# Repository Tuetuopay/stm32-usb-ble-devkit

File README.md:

# STM32 + nRF51 USB & BLE devkit

Small devkit to work with both USB and BLE. Useful for USB Bluetooth gadgets.

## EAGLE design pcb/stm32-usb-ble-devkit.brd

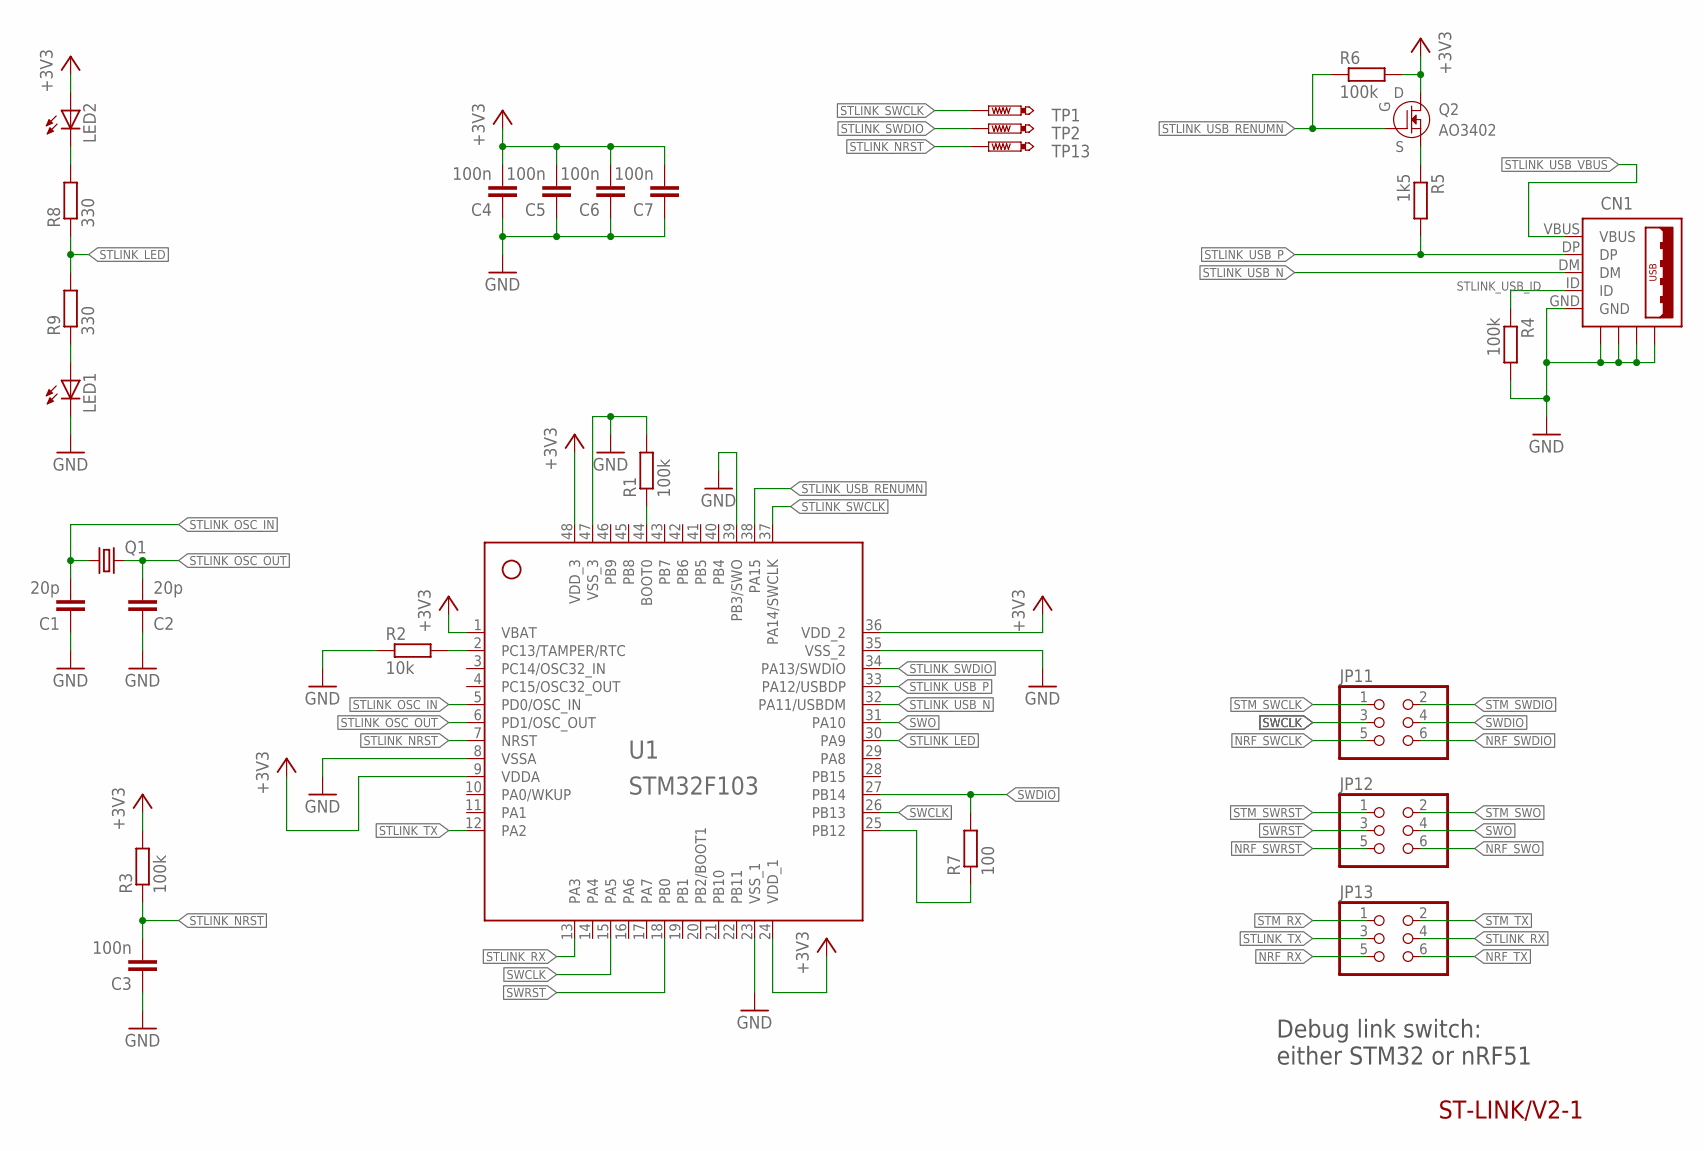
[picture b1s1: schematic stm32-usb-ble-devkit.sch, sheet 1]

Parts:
C1, C2: 20p; 0603
C3, C4, C5, C6, C7: 100n; 0603
CN1: USB-MICROB-2TABS; USB-MICROB-2
JP11, JP12, JP13: PINHD-2X3; 2X03
LED1, LED2: LEDCHIP-LED0603; CHIP-LED0603
Q1: CRYSTALHC49S; HC49/S
Q2: AO3402; SOT23-3
R1, R3, R4, R6: 100k; R0603
R2: 10k; R0603
R5: 1k5; R0603
R7: 100; R0603
R8, R9: 330; R0603
TP1, TP2, TP13: PTR1B1,27; B1,27
U1: STM32F103-48LQFP; LQFP-48

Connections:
+3V3: C4.2, C5.2, C6.2, C7.2, LED2.A, Q2.3 (D), R3.2, R6.2, U1.1 (VBAT), U1.9 (VDDA), U1.24 (VDD_1), U1.36 (VDD_2), U1.48 (VDD_3); also elsewhere on the board
GND: C1.1, C2.1, C3.1, C4.1, C5.1, C6.1, C7.1, CN1.GND, CN1.GND@1 (GND), CN1.GND@2 (GND), CN1.GND@3 (GND), CN1.GND@4 (GND), LED1.C, R1.2, R2.1, R4.2, U1.8 (VSSA), U1.23 (VSS_1), U1.35 (VSS_2), U1.39 (PB3/SWO), U1.47 (VSS_3); also elsewhere on the board
NRF_RX: JP13.5; also elsewhere on the board
NRF_SWCLK: JP11.5; also elsewhere on the board
NRF_SWDIO: JP11.6; also elsewhere on the board
NRF_SWO: JP12.6
NRF_SWRST: JP12.5
NRF_TX: JP13.6; also elsewhere on the board
STLINK_BOOT0: R1.1, U1.44 (BOOT0)
STLINK_LED: R8.1, R9.2, U1.30 (PA9)
STLINK_LED_RB: LED1.A, R9.1
STLINK_LED_RT: LED2.C, R8.2
STLINK_NRST: C3.2, R3.1, TP13.TP, U1.7 (NRST)
STLINK_OSC_IN: C1.2, Q1.1, U1.5 (PD0/OSC_IN)
STLINK_OSC_OUT: C2.2, Q1.2, U1.6 (PD1/OSC_OUT)
STLINK_PC13: R2.2, U1.2 (PC13/TAMPER/RTC)
STLINK_RX: JP13.4, U1.13 (PA3)
STLINK_SWCLK: TP1.TP, U1.37 (PA14/SWCLK)
STLINK_SWDIO: TP2.TP, U1.34 (PA13/SWDIO)
STLINK_SWDIO_PD: R7.1, U1.25 (PB12)
STLINK_TX: JP13.3, U1.12 (PA2)
STLINK_USB_ID: CN1.ID, R4.1
STLINK_USB_N: CN1.DM, U1.32 (PA11/USBDM)
STLINK_USB_P: CN1.DP, R5.2, U1.33 (PA12/USBDP)
STLINK_USB_RENUMN: Q2.1 (G), R6.1, U1.38 (PA15)
STLINK_USB_RENUM_PU: Q2.2 (S), R5.1
STLINK_USB_VBUS: CN1.VBUS; also elsewhere on the board
STM_RX: JP13.1; also elsewhere on the board
STM_SWCLK: JP11.1; also elsewhere on the board
STM_SWDIO: JP11.2; also elsewhere on the board
STM_SWO: JP12.2; also elsewhere on the board
STM_SWRST: JP12.1; also elsewhere on the board
STM_TX: JP13.2; also elsewhere on the board
SWCLK: JP11.3, U1.15 (PA5), U1.26 (PB13)
SWDIO: JP11.4, R7.2, U1.27 (PB14)
SWO: JP12.4, U1.31 (PA10)
SWRST: JP12.3, U1.18 (PB0)

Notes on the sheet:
ST-LINK/V2-1
Debug link switch: either STM32 or nRF51

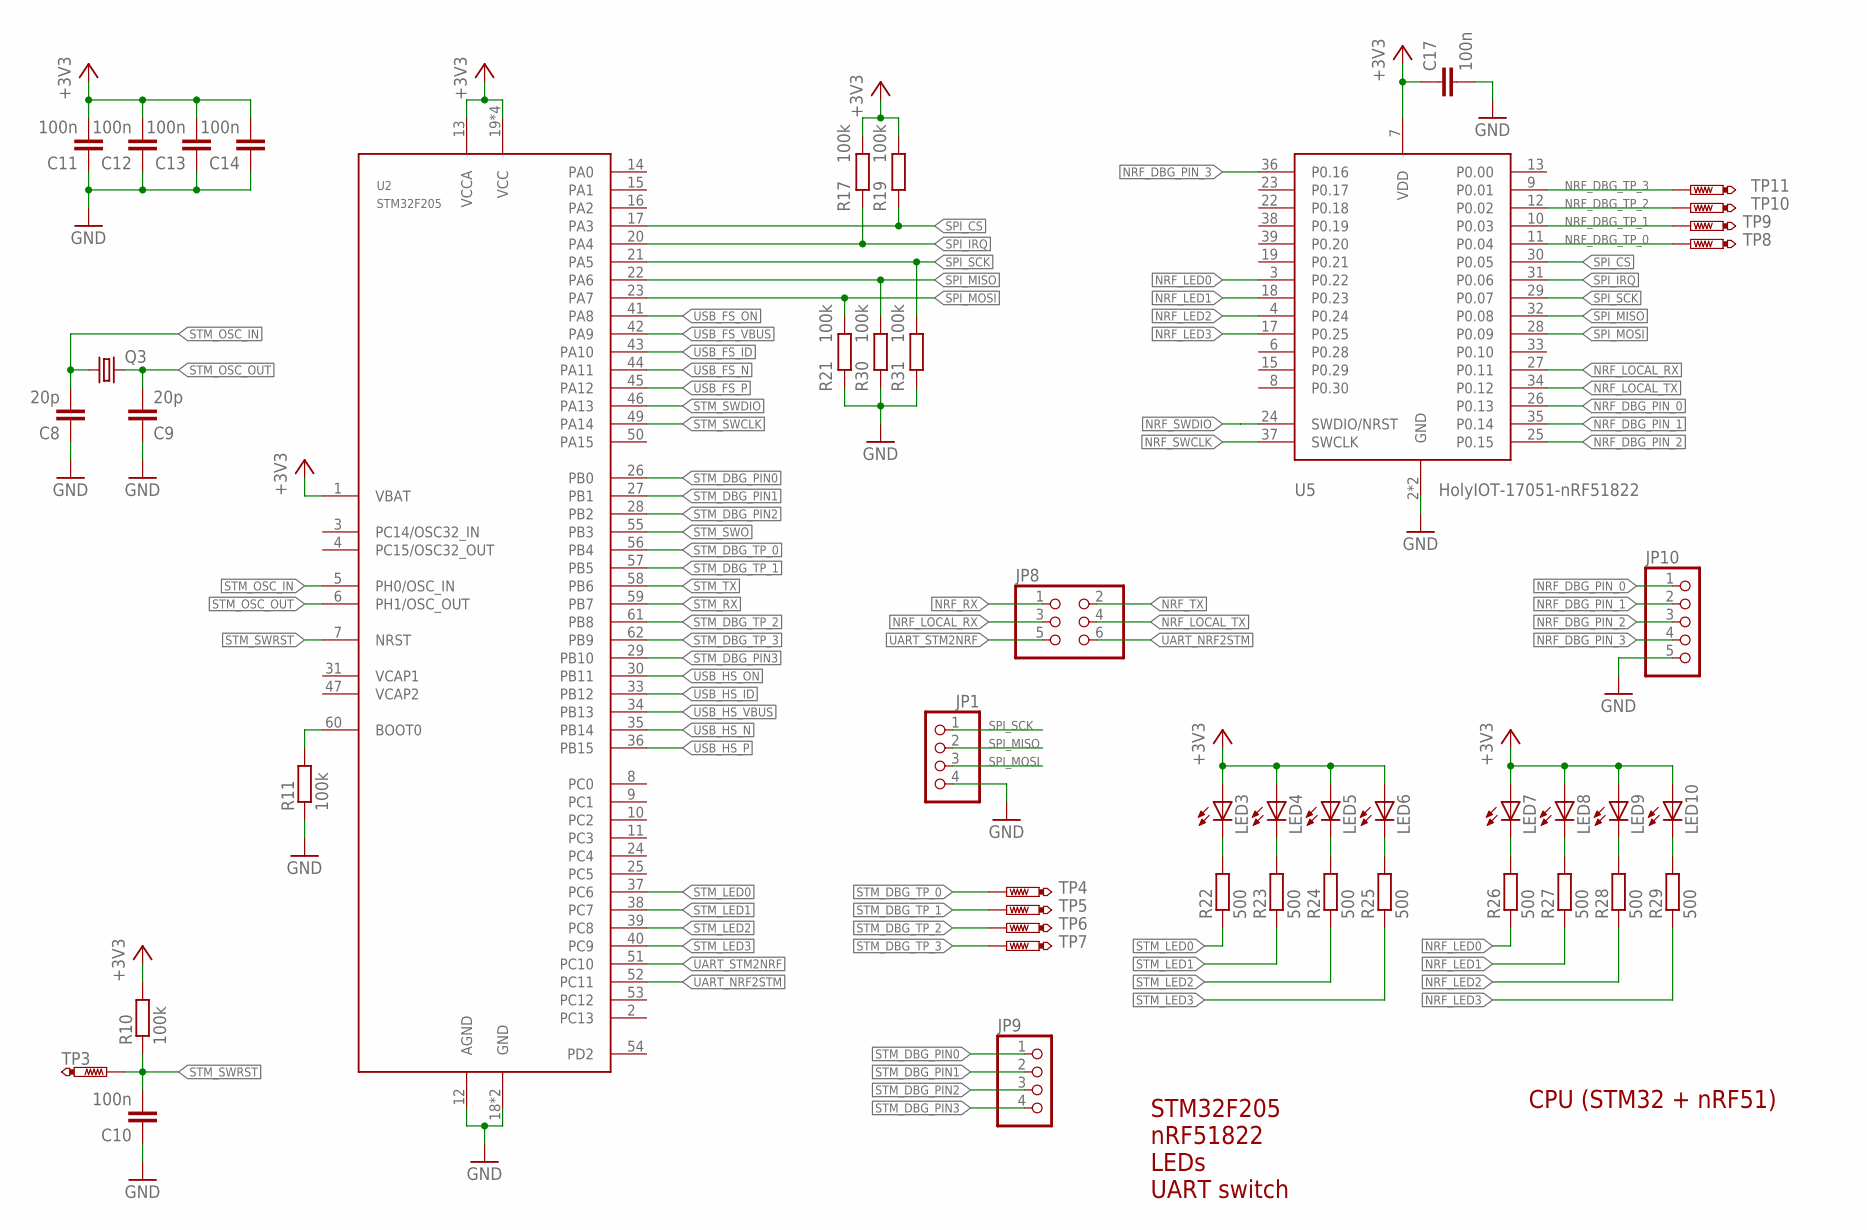
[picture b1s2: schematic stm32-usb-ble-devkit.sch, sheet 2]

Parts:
C8, C9: 20p; 0603
C10, C11, C12, C13, C14, C17: 100n; 0603
JP1, JP9: PINHD-1X4; 1X04
JP8: PINHD-2X3; 2X03
JP10: PINHD-1X5; 1X05
LED3, LED4, LED5, LED6, LED7, LED8, LED9, LED10: LEDCHIP-LED0603; CHIP-LED0603
Q3: CRYSTALHC49S; HC49/S
R10, R11, R17, R19, R21, R30, R31: 100k; R0603
R22, R23, R24, R25, R26, R27, R28, R29: 500; R0603
TP3, TP4, TP5, TP6, TP7, TP8, TP9, TP10, TP11: PTR1B1,27; B1,27
U2: STM32F205-64; LQFP-64
U5: HOLYIOT-17051-NRF51822

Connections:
+3V3: C11.2, C12.2, C13.2, C14.2, C17.1, LED3.A, LED4.A, LED5.A, LED6.A, LED7.A, LED8.A, LED9.A, LED10.A, R10.2, R17.2, R19.2, U2.1 (VBAT), U2.13 (VCCA), U2.19 (VCC), U2.32 (VCC), U2.48 (VCC), U2.64 (VCC), U5.7 (VDD); also elsewhere on the board
BOOT0: R11.2, U2.60 (BOOT0)
GND: C8.1, C9.1, C10.1, C11.1, C12.1, C13.1, C14.1, C17.2, JP1.4, JP10.5, R11.1, R21.1, R30.1, R31.1, U2.12 (AGND), U2.18 (GND), U2.63 (GND), U5.2 (GND), U5.14 (GND); also elsewhere on the board
NRF_DBG_PIN_0: JP10.1, U5.26 (P0.13)
NRF_DBG_PIN_1: JP10.2, U5.35 (P0.14)
NRF_DBG_PIN_2: JP10.3, U5.25 (P0.15)
NRF_DBG_PIN_3: JP10.4, U5.36 (P0.16)
NRF_DBG_TP_0: TP8.TP, U5.11 (P0.04)
NRF_DBG_TP_1: TP9.TP, U5.10 (P0.03)
NRF_DBG_TP_2: TP10.TP, U5.12 (P0.02)
NRF_DBG_TP_3: TP11.TP, U5.9 (P0.01)
NRF_LED0: R26.1, U5.3 (P0.22)
NRF_LED1: R27.1, U5.18 (P0.23)
NRF_LED2: R28.1, U5.4 (P0.24)
NRF_LED3: R29.1, U5.17 (P0.25)
NRF_LEDR0: LED7.C, R26.2
NRF_LEDR1: LED8.C, R27.2
NRF_LEDR2: LED9.C, R28.2
NRF_LEDR3: LED10.C, R29.2
NRF_LOCAL_RX: JP8.3, U5.27 (P0.11)
NRF_LOCAL_TX: JP8.4, U5.34 (P0.12)
NRF_RX: JP8.1; also elsewhere on the board
NRF_SWCLK: U5.37 (SWCLK); also elsewhere on the board
NRF_SWDIO: U5.24 (SWDIO/NRST); also elsewhere on the board
NRF_TX: JP8.2; also elsewhere on the board
SPI_CS: R19.1, U2.17 (PA3), U5.30 (P0.05)
SPI_IRQ: R17.1, U2.20 (PA4), U5.31 (P0.06)
SPI_MISO: JP1.2, R30.2, U2.22 (PA6), U5.32 (P0.08)
SPI_MOSI: JP1.3, R21.2, U2.23 (PA7), U5.28 (P0.09)
SPI_SCK: JP1.1, R31.2, U2.21 (PA5), U5.29 (P0.07)
STM_DBG_PIN0: JP9.1, U2.26 (PB0)
STM_DBG_PIN1: JP9.2, U2.27 (PB1)
STM_DBG_PIN2: JP9.3, U2.28 (PB2)
STM_DBG_PIN3: JP9.4, U2.29 (PB10)
STM_DBG_TP_0: TP4.TP, U2.56 (PB4)
STM_DBG_TP_1: TP5.TP, U2.57 (PB5)
STM_DBG_TP_2: TP6.TP, U2.61 (PB8)
STM_DBG_TP_3: TP7.TP, U2.62 (PB9)
STM_LED0: R22.1, U2.37 (PC6)
STM_LED1: R23.1, U2.38 (PC7)
STM_LED2: R24.1, U2.39 (PC8)
STM_LED3: R25.1, U2.40 (PC9)
STM_LEDR0: LED3.C, R22.2
STM_LEDR1: LED4.C, R23.2
STM_LEDR3: LED6.C, R25.2
STM_LEDR_2: LED5.C, R24.2
STM_OSC_IN: C8.2, Q3.1, U2.5 (PH0/OSC_IN)
STM_OSC_OUT: C9.2, Q3.2, U2.6 (PH1/OSC_OUT)
STM_RX: U2.59 (PB7); also elsewhere on the board
STM_SWCLK: U2.49 (PA14); also elsewhere on the board
STM_SWDIO: U2.46 (PA13); also elsewhere on the board
STM_SWO: U2.55 (PB3); also elsewhere on the board
STM_SWRST: C10.2, R10.1, TP3.TP, U2.7 (NRST); also elsewhere on the board
STM_TX: U2.58 (PB6); also elsewhere on the board
UART_NRF2STM: JP8.6, U2.52 (PC11)
UART_STM2NRF: JP8.5, U2.51 (PC10)
USB_FS_ID: U2.43 (PA10); also elsewhere on the board
USB_FS_N: U2.44 (PA11); also elsewhere on the board
USB_FS_ON: U2.41 (PA8); also elsewhere on the board
USB_FS_P: U2.45 (PA12); also elsewhere on the board
USB_FS_VBUS: U2.42 (PA9); also elsewhere on the board
USB_HS_ID: U2.33 (PB12); also elsewhere on the board
USB_HS_N: U2.35 (PB14); also elsewhere on the board
USB_HS_ON: U2.30 (PB11); also elsewhere on the board
USB_HS_P: U2.36 (PB15); also elsewhere on the board
USB_HS_VBUS: U2.34 (PB13); also elsewhere on the board

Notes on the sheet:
CPU (STM32 + nRF51)
STM32F205 nRF51822 LEDs UART switch

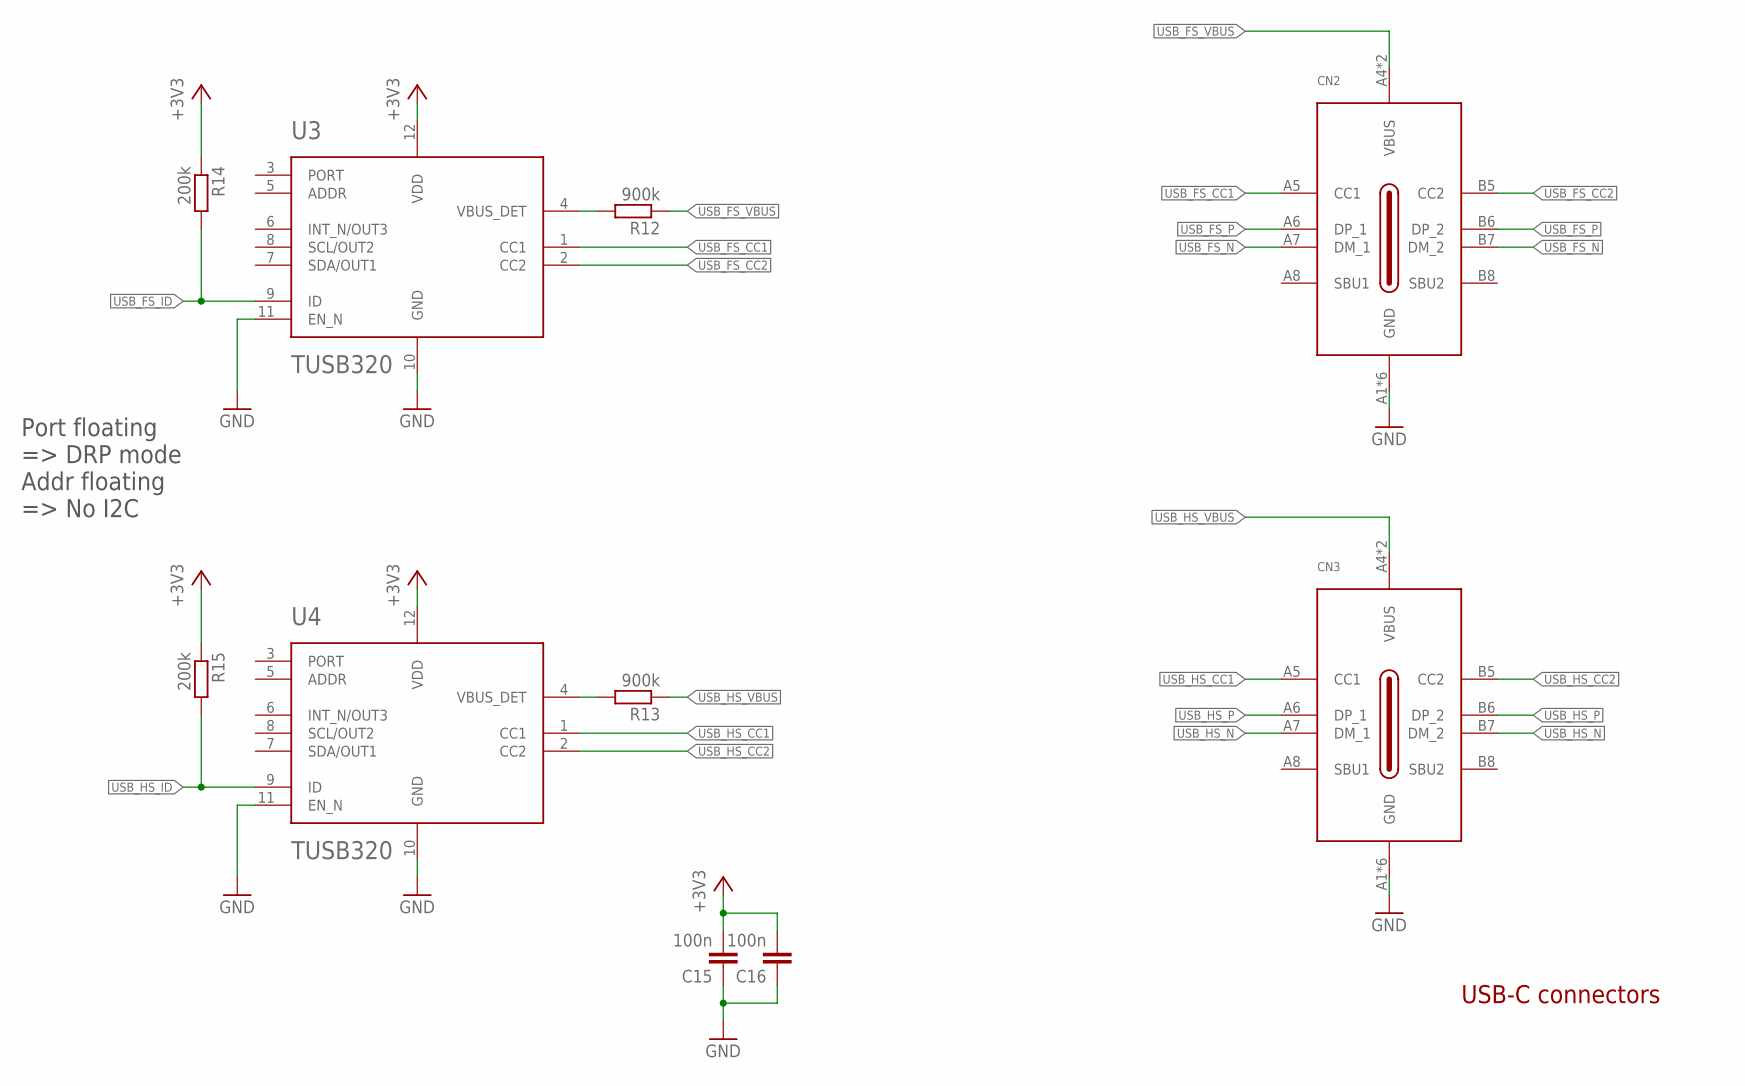
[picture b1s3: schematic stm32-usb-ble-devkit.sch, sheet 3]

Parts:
C15, C16: 100n; 0603
CN2, CN3: USB-C-2.0-FEMALE; USB-C-FEMALE
R12, R13: 900k; R0603
R14, R15: 200k; R0603
U3, U4: TUSB320; X2QFN-0.4

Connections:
+3V3: C15.2, C16.2, R14.1, R15.1, U3.12 (VDD), U4.12 (VDD); also elsewhere on the board
GND: C15.1, C16.1, CN2.A1 (GND), CN2.A12 (GND), CN2.G1 (GND), CN2.G2 (GND), CN2.G3 (GND), CN2.G4 (GND), CN3.A1 (GND), CN3.A12 (GND), CN3.G1 (GND), CN3.G2 (GND), CN3.G3 (GND), CN3.G4 (GND), U3.10 (GND), U3.11 (EN_N), U4.10 (GND), U4.11 (EN_N); also elsewhere on the board
USB_FS_CC1: CN2.A5 (CC1), U3.1 (CC1)
USB_FS_CC2: CN2.B5 (CC2), U3.2 (CC2)
USB_FS_ID: R14.2, U3.9 (ID); also elsewhere on the board
USB_FS_N: CN2.A7 (DM_1), CN2.B7 (DM_2); also elsewhere on the board
USB_FS_P: CN2.A6 (DP_1), CN2.B6 (DP_2); also elsewhere on the board
USB_FS_VBUS: CN2.A4 (VBUS), CN2.A9 (VBUS), R12.1; also elsewhere on the board
USB_FS_VBUS_DET: R12.2, U3.4 (VBUS_DET)
USB_HS_CC1: CN3.A5 (CC1), U4.1 (CC1)
USB_HS_CC2: CN3.B5 (CC2), U4.2 (CC2)
USB_HS_ID: R15.2, U4.9 (ID); also elsewhere on the board
USB_HS_N: CN3.A7 (DM_1), CN3.B7 (DM_2); also elsewhere on the board
USB_HS_P: CN3.A6 (DP_1), CN3.B6 (DP_2); also elsewhere on the board
USB_HS_VBUS: CN3.A4 (VBUS), CN3.A9 (VBUS), R13.1; also elsewhere on the board
USB_HS_VBUS_DET: R13.2, U4.4 (VBUS_DET)

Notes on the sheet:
Port floating => DRP mode Addr floating => No I2C
USB-C connectors

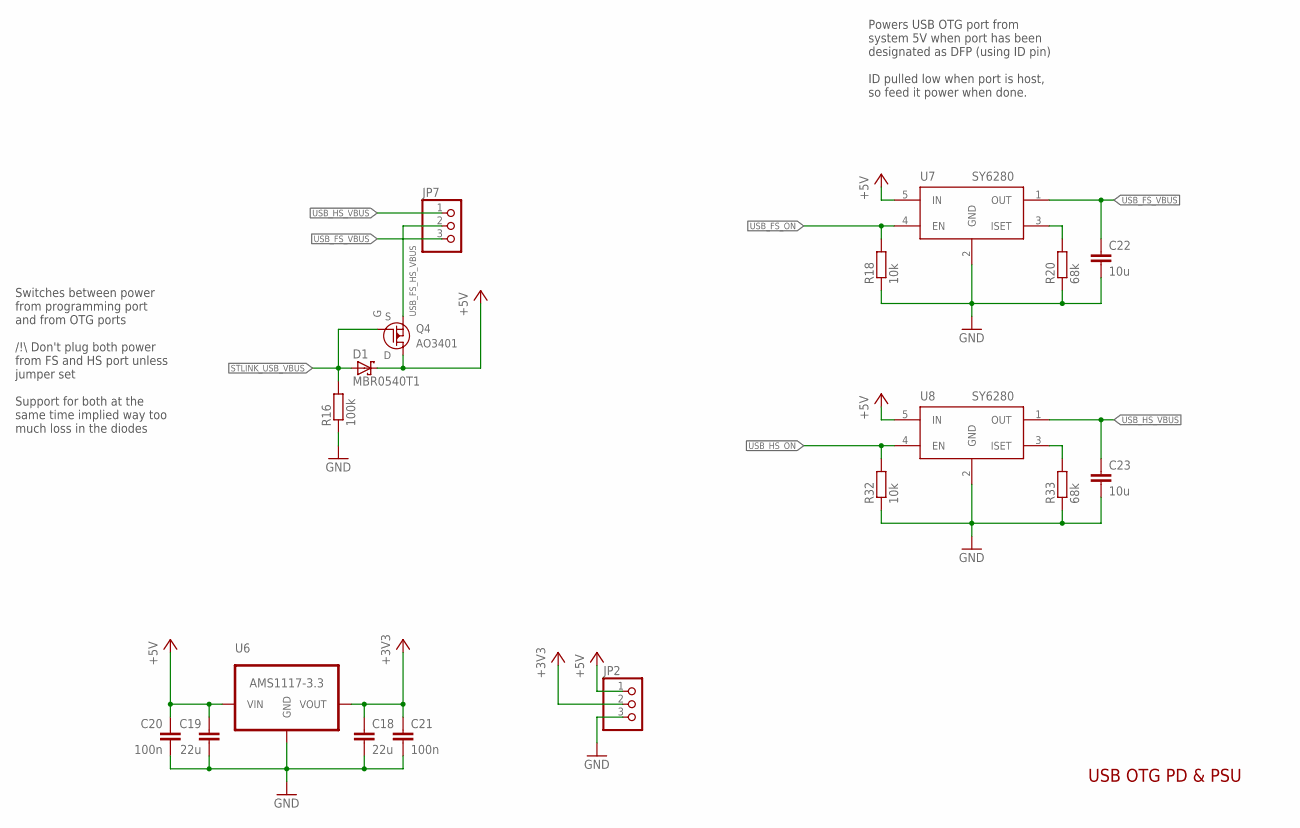
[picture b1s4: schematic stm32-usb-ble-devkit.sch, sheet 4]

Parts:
C18, C19: 22u; 0603
C20, C21: 100n; 0603
C22, C23: 10u; 0603
D1: MBR0540T1; SOD123
JP2, JP7: PINHD-1X3; 1X03
Q4: AO3401; SOT23-3
R16: 100k; R0603
R18, R32: 10k; R0603
R20, R33: 68k; R0603
U6: AMS1117-3.3; SOT223
U7, U8: SY6280; SOT23-5

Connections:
+3V3: C18.1, C21.1, JP2.2, U6.2 (VOUT); also elsewhere on the board
+5V: C19.1, C20.1, D1.C, JP2.1, Q4.3 (D), U6.3 (VIN), U7.5 (IN), U8.5 (IN)
GND: C18.2, C19.2, C20.2, C21.2, C22.2, C23.2, JP2.3, R16.1, R18.1, R20.1, R32.1, R33.1, U6.1 (GND), U7.2 (GND), U8.2 (GND); also elsewhere on the board
STLINK_USB_VBUS: D1.A, Q4.1 (G), R16.2; also elsewhere on the board
USB_FS_HS_VBUS: JP7.2, Q4.2 (S)
USB_FS_ISET: R20.2, U7.3 (ISET)
USB_FS_ON: R18.2, U7.4 (EN); also elsewhere on the board
USB_FS_VBUS: C22.1, JP7.3, U7.1 (OUT); also elsewhere on the board
USB_HS_ISET: R33.2, U8.3 (ISET)
USB_HS_ON: R32.2, U8.4 (EN); also elsewhere on the board
USB_HS_VBUS: C23.1, JP7.1, U8.1 (OUT); also elsewhere on the board

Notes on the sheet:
USB OTG PD & PSU
Switches between power from programming port and from OTG ports /\!\\ Don't plug both power from FS and HS port unless jumper set Support for both at the same time implied way too much loss in the diodes
Powers USB OTG port from system 5V when port has been designated as DFP (using ID pin) ID pulled low when port is host, so feed it power when done.

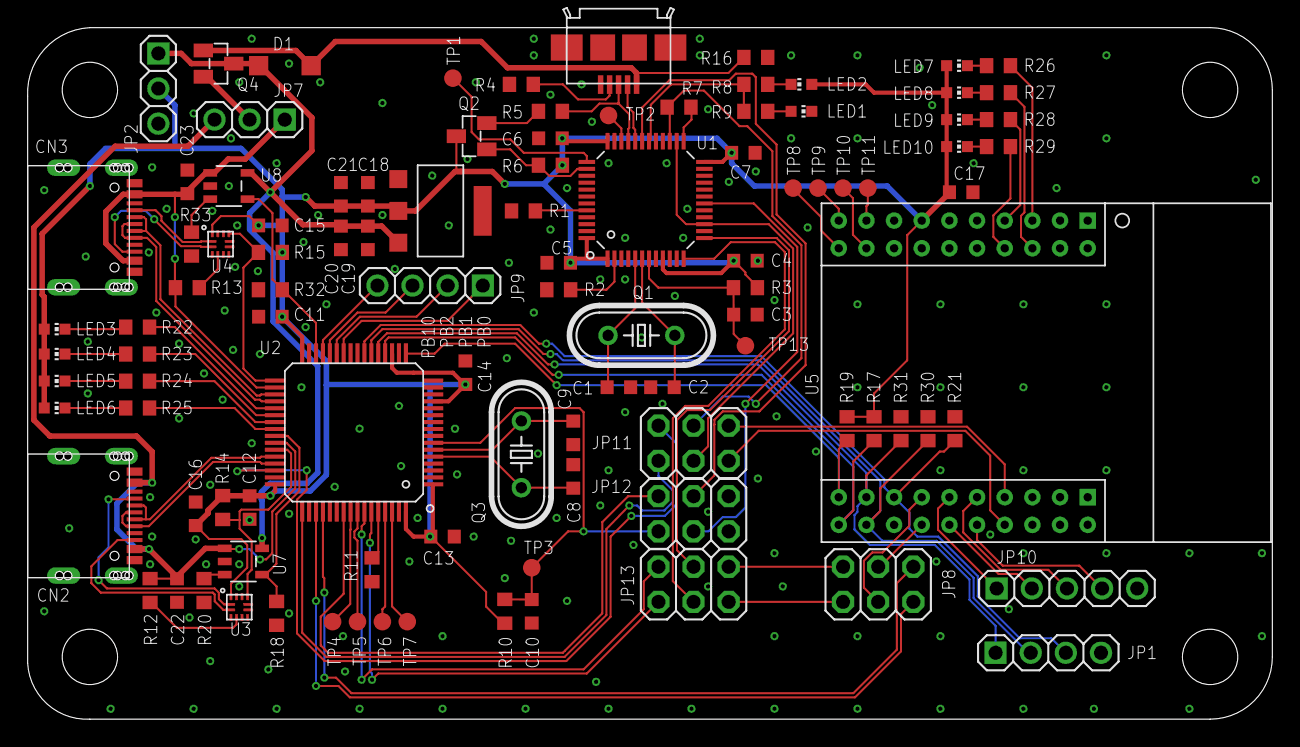
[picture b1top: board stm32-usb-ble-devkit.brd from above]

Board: 2 copper layers, 90.0 x 50.0 mm, 103 parts (0 on the bottom side), 99 nets.

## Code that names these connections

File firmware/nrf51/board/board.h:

/*
    Copyright (C) 2015 Fabio Utzig

    Licensed under the Apache License, Version 2.0 (the "License");
    you may not use this file except in compliance with the License.
    You may obtain a copy of the License at

        http://www.apache.org/licenses/LICENSE-2.0

    Unless required by applicable law or agreed to in writing, software
    distributed under the License is distributed on an "AS IS" BASIS,
    WITHOUT WARRANTIES OR CONDITIONS OF ANY KIND, either express or implied.
    See the License for the specific language governing permissions and
    limitations under the License.
*/

#ifndef _BOARD_H_
#define _BOARD_H_

/* Board identifier. */
#define BOARD_STM32_USB_BLE_DEVKIT
#define BOARD_NAME              "STM32+nRF51 USB+BLE Devkit"

/* Board oscillators-related settings. */
#define NRF51_XTAL_VALUE        16000000

/* GPIO pins. */
#define DBG_TP3        1
#define DBG_TP2        2
#define DBG_TP1        3
#define DBG_TP0        4
#define SPI_CS         5
#define SPI_IRQ        6
#define SPI_SCK        7
#define SPI_MISO       8
#define SPI_MOSI       9
#define UART_RX        11
#define UART_TX        12
#define DBG_P0         13
#define DBG_P1         14
#define DBG_P2         15
#define DBG_P3         16
#define LED0           22
#define LED1           23
#define LED2           24
#define LED3           25

/*
 * IO pins assignments.
 */
#define IOPORT1_DBG_TP3        1U
#define IOPORT1_DBG_TP2        2U
#define IOPORT1_DBG_TP1        3U
#define IOPORT1_DBG_TP0        4U
#define IOPORT1_SPI_CS         5U
#define IOPORT1_SPI_IRQ        6U
#define IOPORT1_SPI_SCK        7U
#define IOPORT1_SPI_MISO       8U
#define IOPORT1_SPI_MOSI       9U
#define IOPORT1_UART_RX        11U
#define IOPORT1_UART_TX        12U
#define IOPORT1_DBG_P0         13U
#define IOPORT1_DBG_P1         14U
#define IOPORT1_DBG_P2         15U
#define IOPORT1_DBG_P3         16U
#define IOPORT1_LED0           22U
#define IOPORT1_LED1           23U
#define IOPORT1_LED2           24U
#define IOPORT1_LED3           25U

/*
 * IO lines assignments.
 */
#define LINE_DBG_TP3        PAL_LINE(IOPORT1, 1U)
#define LINE_DBG_TP2        PAL_LINE(IOPORT1, 2U)
#define LINE_DBG_TP1        PAL_LINE(IOPORT1, 3U)
#define LINE_DBG_TP0        PAL_LINE(IOPORT1, 4U)
#define LINE_SPI_CS         PAL_LINE(IOPORT1, 5U)
#define LINE_SPI_IRQ        PAL_LINE(IOPORT1, 6U)
#define LINE_SPI_SCK        PAL_LINE(IOPORT1, 7U)
#define LINE_SPI_MISO       PAL_LINE(IOPORT1, 8U)
#define LINE_SPI_MOSI       PAL_LINE(IOPORT1, 9U)
#define LINE_UART_RX        PAL_LINE(IOPORT1, 11U)
#define LINE_UART_TX        PAL_LINE(IOPORT1, 12U)
#define LINE_DBG_P0         PAL_LINE(IOPORT1, 13U)
#define LINE_DBG_P1         PAL_LINE(IOPORT1, 14U)
#define LINE_DBG_P2         PAL_LINE(IOPORT1, 15U)
#define LINE_DBG_P3         PAL_LINE(IOPORT1, 16U)
#define LINE_LED0           PAL_LINE(IOPORT1, 22U)
#define LINE_LED1           PAL_LINE(IOPORT1, 23U)
#define LINE_LED2           PAL_LINE(IOPORT1, 24U)
#define LINE_LED3           PAL_LINE(IOPORT1, 25U)

#if !defined(_FROM_ASM_)
#ifdef __cplusplus
extern "C" {
#endif
void boardInit(void);
#ifdef __cplusplus
}
#endif
#endif /* _FROM_ASM_ */

#endif /* _BOARD_H_ */

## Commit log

2018-09-04 Add schematic first shot
2018-09-04 Add PCB first shot
2018-09-05 pcb: Update USB-C connector footprint
2018-09-05 pcb: Finish routing (including 3v3 and 5v)
2018-09-05 pcb: Unhide GND airwires
2018-09-05 pcb: Fix symbol orientation and add PSU caps
2018-09-05 pcb: Done groundplane
2018-09-06 pcb: Add proper CAM settings
2018-09-06 pcb: Approve resistor keepout DRC violations
    I don't plan to assemble this board with a pick and place, which those
    keepouts are made for.
2018-09-06 pcb: Add SPI PU/PD resistors
2018-09-06 pcb: Add Makefile to easily generate output files
2018-09-07 pcb: Fix GND thermals size
2018-09-08 pcb: Add more GND vias
2018-09-15 Fix via size (6mm diam instead of 9)
2018-10-27 pcb: Make USB-C pads stick out more from the footprint
2018-10-27 pcb: Fix ST-LINK BOOT0 resistor
2018-10-27 pcb: Fix STM32 VCAP pins
2018-10-27 pcb: Fix corner hole sizes (proper M4)
2018-10-27 pcb: Misc changes following via size fix
2018-10-27 pcb: Add USB VBUS detection and USB BUS ON
2018-10-27 pcb: Increased space between USB-C connectors
2018-10-27 pcb: Replaced PSU BAS16 with better diode
2018-10-27 pcb: Replace PSU 0805 caps with 0603
2018-10-27 pcb: Switch OTG PSU MOSFET to dedicated IC
2018-10-27 pcb: Fix LQFP64 silkscreen
2018-10-27 pcb: GND plane improvements
2018-10-28 pcb/Makefile: Fix typo
2018-10-28 pcb: Misc GND fixups
2018-10-28 pcb: Add Harold Bluetooth to bottom silkscreen
2018-10-28 pcb: Slightly shifted USB-HS up
2018-11-01 pcb: Switch headers to round pads
2018-11-01 pcb: Moved all nRF TP to the same side
2018-11-01 pcb: Add SPI header
2018-11-01 pcb: Add header exposing supply voltages
2018-11-01 pcb: Make all silkscreen text the same thickness
2018-11-03 fw: Add basic nrf51 project (blinkenlights)
2018-11-03 fw: Add basic stm32 project (blinkenlights)
2018-11-05 pcb: Fix some GND antennas
2018-11-20 fw/stm32: Update board file to pcb-v1.1
2018-12-15 stm32: Move main to dedicated src folder
2018-12-15 stm32: Add logger class
2018-12-15 stm32: Upgrade to ChibiOS 18.2.x
2018-12-15 stm32: Make logger thread safe
2018-12-16 stm32/usb: Add arbiter to handle OTG transitions
2018-12-16 Add Drone CI
2018-12-16 stm32/usb: Add host driver
    Dumps HID events to serial port
2018-12-16 stm32/usb/host: Fix ring buffer
2018-12-16 stm32: Add US keyboard layout to log letters
2018-12-16 stm32/usb/arbiter: Simulate OTG event at boot
    This allows to get the initial state of OTG ports (e.g. bootup with
    something already plugged in, or being powered by an OTG port).
2018-12-16 CI: Switch to my ChibiOS fork
2018-12-19 stm32/usb: Add USB HID keyboard device
    This adds the USB configuration, enumeration, synchronization with
    keyboards plugged in, etc...
2018-12-19 stm32/usb/hid_dev_cfg: Cleanup test stuff
2018-12-19 stm32/usb/host: Sync keyboard LED state with internal one
